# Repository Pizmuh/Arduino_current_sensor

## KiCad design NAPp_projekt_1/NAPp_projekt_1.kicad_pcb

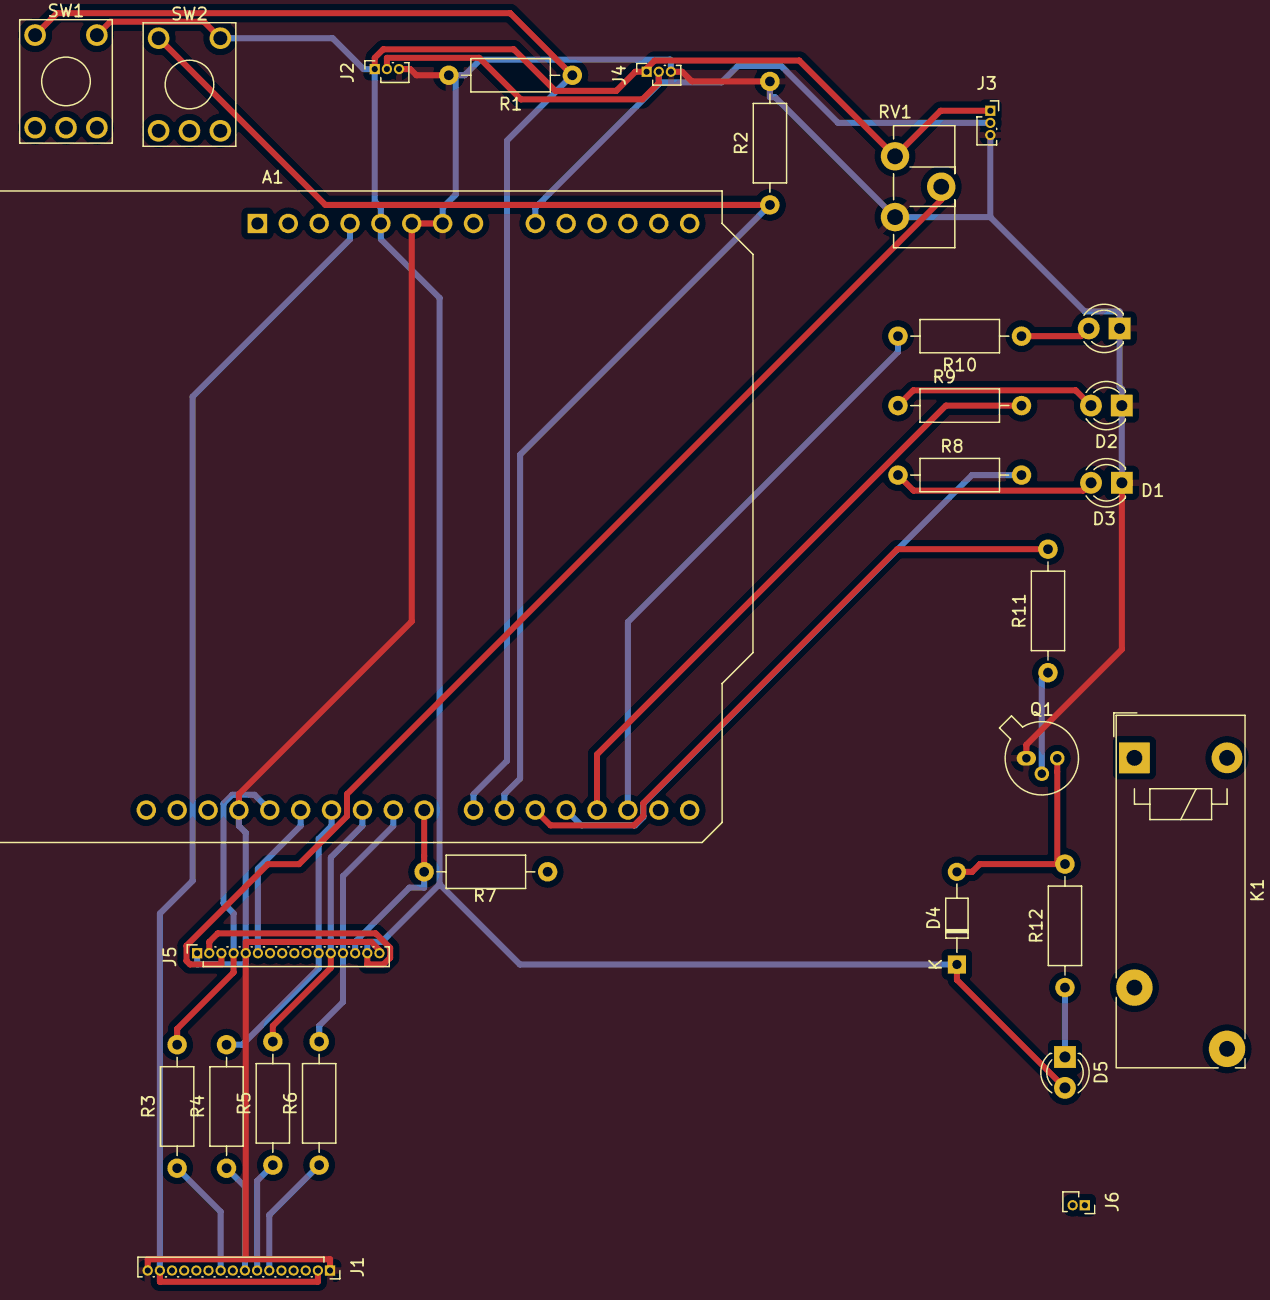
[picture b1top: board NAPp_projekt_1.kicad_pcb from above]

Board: 2 copper layers, 29 parts (0 on the bottom side), 27 nets.

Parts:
A1: Arduino_UNO_R3
D1: rd.; LED_D3.0mm
D2: ru.; LED_D3.0mm
D3: ze.; LED_D3.0mm
D4: D; D_DO-34_SOD68_P7.62mm_Horizontal
D5: LED; LED_D3.0mm
J1, J5: Conn_01x16_Female; PinSocket_1x16_P1.00mm_Vertical
J2, J3, J4: Conn_01x03_Female; PinSocket_1x03_P1.00mm_Vertical
J6: Conn_01x02_Female; PinSocket_1x02_P1.00mm_Vertical
K1: AZ850-x; Relay_1-Form-A_Schrack-RYII_RM5mm
Q1: BC107; TO-18-3
R1, R2: 10k; R_Axial_DIN0207_L6.3mm_D2.5mm_P10.16mm_Horizontal
R3, R4, R5, R6, R7, R11, R12: R; R_Axial_DIN0207_L6.3mm_D2.5mm_P10.16mm_Horizontal
R8, R9, R10: 470R; R_Axial_DIN0207_L6.3mm_D2.5mm_P10.16mm_Horizontal
RV1: R_Potentiometer; Potentiometer_ACP_CA9-H3,8_Horizontal
SW1, SW2: SW_Push; KSA_Tactile_SPST

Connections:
+3V3: A1.4 (3V3), J1.2, J1.15
+5V: A1.5 (+5V), D4.1 (K), D5.2 (A), J2.1, J3.1, J4.1, J5.2, J5.15, RV1.1, SW1.2, SW2.2
A0: A1.9 (A0), J2.2, J3.2, J4.2
D5: A1.20 (D5), R11.2
D6: A1.21 (D6), R2.1, SW2.1
D7: A1.22 (D7), R1.1, SW1.1
D9: J1.6, R6.1
D10: J1.7, R5.1
D11: J1.8, R4.1
D13: J1.10, R3.1
GND: A1.6 (GND), A1.7 (GND), A1.29 (GND), D1.1 (K), D2.1 (K), D3.1 (K), J1.1, J1.16, J2.3, J3.3, J4.3, J5.1, J5.5, J5.16, Q1.1 (E), R1.2, R2.2, RV1.3
unnamed: A1.17 (D2), R10.2
unnamed: A1.18 (D3), R9.2
unnamed: A1.19 (D4), R8.2
unnamed: A1.23 (D8), J5.14, R7.2
unnamed: A1.24 (D9), J5.13, R6.2
unnamed: A1.25 (D10), J5.12, R5.2
unnamed: A1.26 (D11), J5.11, R4.2
unnamed: A1.27 (D12), J5.6
unnamed: A1.28 (D13), J5.4, R3.2
unnamed: D1.2 (A), R8.1
unnamed: D2.2 (A), R9.1
unnamed: D3.2 (A), R10.1
unnamed: D4.2 (A), Q1.3 (C), R12.2
unnamed: D5.1 (K), R12.1
unnamed: J5.3, RV1.2
unnamed: Q1.2 (B), R11.1
